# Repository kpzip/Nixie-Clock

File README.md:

# Nixie-Clock
Clock using IN-16 Nixie Tubes

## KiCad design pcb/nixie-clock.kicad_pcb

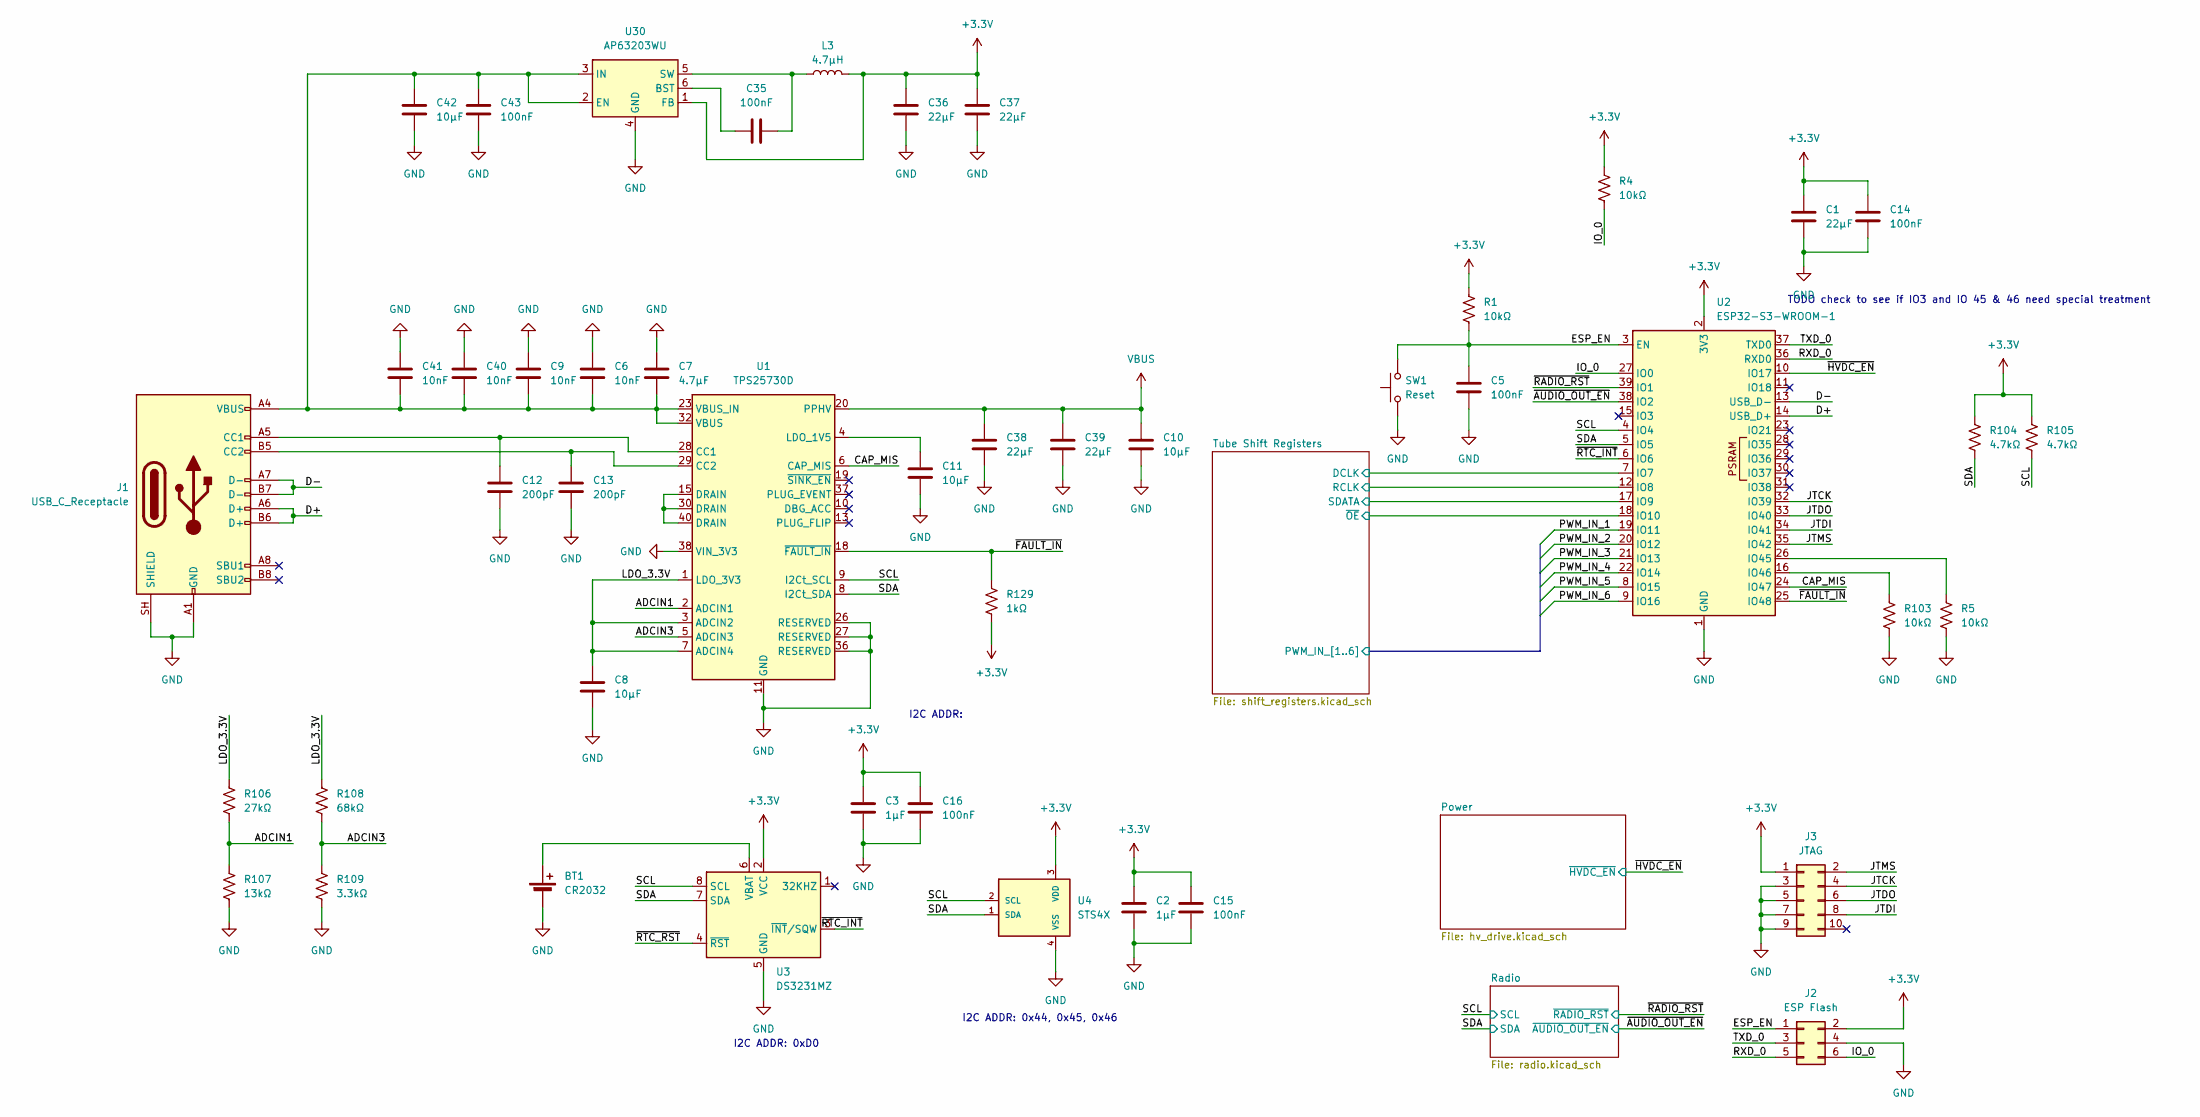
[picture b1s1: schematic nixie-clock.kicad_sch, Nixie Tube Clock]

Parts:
BT1: CR2032; BatteryHolder_MPD_BC2003_1x2032
C1, C36, C37, C38, C39: 22μF; C_0805_2012Metric
C2, C3: 1μF; C_0603_1608Metric
C5, C14, C15, C16, C35, C43: 100nF; C_0603_1608Metric
C6, C9, C40, C41: 10nF; C_0603_1608Metric
C7: 4.7μF; C_0805_2012Metric
C8, C10, C11, C42: 10μF; C_0805_2012Metric
C12, C13: 200pF; C_0603_1608Metric
J1: USB_C_Receptacle; USB_C_Receptacle_GCT_USB4105-xx-A_16P_TopMnt_Horizontal; Manufacturer Part Number USB4105-GF-A
J2: ESP Flash; IDC-Header_2x03_P2.54mm_Vertical
J3: JTAG; IDC-Header_2x05_P2.54mm_Vertical
L3: 4.7μH; L_0603_1608Metric_Pad1.05x0.95mm_HandSolder; Manufacturer Part Number LQM18PN4R7MFRL
R1, R4, R5, R103: 10kΩ; R_0603_1608Metric
R104, R105: 4.7kΩ; R_0603_1608Metric
R106: 27kΩ; R_0603_1608Metric
R107: 13kΩ; R_0603_1608Metric
R108: 68kΩ; R_0603_1608Metric
R109: 3.3kΩ; R_0603_1608Metric
R129: 1kΩ; R_0603_1608Metric
SW1: Reset; SW_PUSH_6mm; Manufacturer Part Number PTS645SL43-2 LFS
U1: TPS25730D; Texas_REF0038A_WQFN-38-2EP_6x4mm_P0.4
U2: ESP32-S3-WROOM-1; Manufacturer Part Number ESP32-S3-WROOM-1-N8R8
U3: DS3231MZ; SOIC-8_3.9x4.9mm_P1.27mm
U4: STS4X
U30: AP63203WU; TSOT-23-6

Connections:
+3.3V: C1.1, C2.1, C3.1, C14.1, C15.1, C16.1, C36.2, C37.2, J2.2, J3.1, L3.2, R1.1, R4.1, R104.1, R105.1, R129.2, U2.2 (3V3), U3.2 (VCC), U4.3 (VDD), U30.1 (FB); also elsewhere on the board
/ADCIN1: R106.2, R107.1, U1.2 (ADCIN1)
/ADCIN3: R108.2, R109.1, U1.5 (ADCIN3)
/CAP_MIS: U1.6 (CAP_MIS), U2.24 (IO47)
/D+: J1.A6 (D+), J1.B6 (D+), U2.14 (USB_D+)
/D-: J1.A7 (D-), J1.B7 (D-), U2.13 (USB_D-)
/ESP_EN: C5.1, J2.1, R1.2, SW1.2, U2.3 (EN)
/IO_0: J2.6, R4.2, U2.27 (IO0)
/JTCK: J3.4, U2.32 (IO39)
/JTDI: J3.8, U2.34 (IO41)
/JTDO: J3.6, U2.33 (IO40)
/JTMS: J3.2, U2.35 (IO42)
/LDO_3.3V: C8.2, R106.1, R108.1, U1.1 (LDO_3V3), U1.3 (ADCIN2), U1.7 (ADCIN4)
/RXD_0: J2.5, U2.36 (RXD0)
/SCL: R105.2, U1.9 (I2Ct_SCL), U2.4 (IO4), U3.8 (SCL), U4.2 (SCL); also elsewhere on the board
/SDA: R104.2, U1.8 (I2Ct_SDA), U2.5 (IO5), U3.7 (SDA), U4.1 (SDA); also elsewhere on the board
/TXD_0: J2.3, U2.37 (TXD0)
/Tube Shift Registers/DCLK: U2.7 (IO7); also elsewhere on the board
/Tube Shift Registers/PWM_IN_1: U2.19 (IO11); also elsewhere on the board
/Tube Shift Registers/PWM_IN_2: U2.20 (IO12); also elsewhere on the board
/Tube Shift Registers/PWM_IN_3: U2.21 (IO13); also elsewhere on the board
/Tube Shift Registers/PWM_IN_4: U2.22 (IO14); also elsewhere on the board
/Tube Shift Registers/PWM_IN_5: U2.8 (IO15); also elsewhere on the board
/Tube Shift Registers/PWM_IN_6: U2.9 (IO16); also elsewhere on the board
/Tube Shift Registers/RCLK: U2.12 (IO8); also elsewhere on the board
/Tube Shift Registers/SDATA: U2.17 (IO9); also elsewhere on the board
/Tube Shift Registers/~OE: U2.18 (IO10); also elsewhere on the board
/~AUDIO_OUT_EN: U2.38 (IO2); also elsewhere on the board
/~FAULT_IN: R129.1, U1.18 (~FAULT_IN), U2.25 (IO48)
/~HVDC_EN: U2.10 (IO17); also elsewhere on the board
/~RADIO_RST: U2.39 (IO1); also elsewhere on the board
/~RTC_INT: U2.6 (IO6), U3.3 (~INT/SQW)
/~RTC_RST: U3.4 (~RST)
unnamed: BT1.1 (+), U3.6 (VBAT)
unnamed: C12.2, J1.A5 (CC1), U1.28 (CC1)
unnamed: C13.2, J1.B5 (CC2), U1.29 (CC2)
unnamed: U1.15 (DRAIN), U1.30 (DRAIN), U1.40 (DRAIN)
unnamed: C11.1, U1.4 (LDO_1V5)
unnamed: C6.2, C7.2, C9.2, C40.2, C41.2, C42.1, C43.1, J1.A4 (VBUS), J1.A9 (VBUS), J1.B4 (VBUS), J1.B9 (VBUS), U1.23 (VBUS_IN), U1.32 (VBUS), U30.2 (EN), U30.3 (IN)
unnamed: R5.1, U2.26 (IO45)
unnamed: R103.1, U2.16 (IO46)
unnamed: C35.1, U30.6 (BST)
unnamed: C35.2, L3.1, U30.5 (SW)
VBUS: C10.1, C38.2, C39.2, U1.20 (PPHV); also elsewhere on the board

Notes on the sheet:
I2C ADDR: 0x44, 0x45, 0x46
TODO check to see if IO3 and IO 45 & 46 need special treatment
I2C ADDR: 0xD0
I2C ADDR:

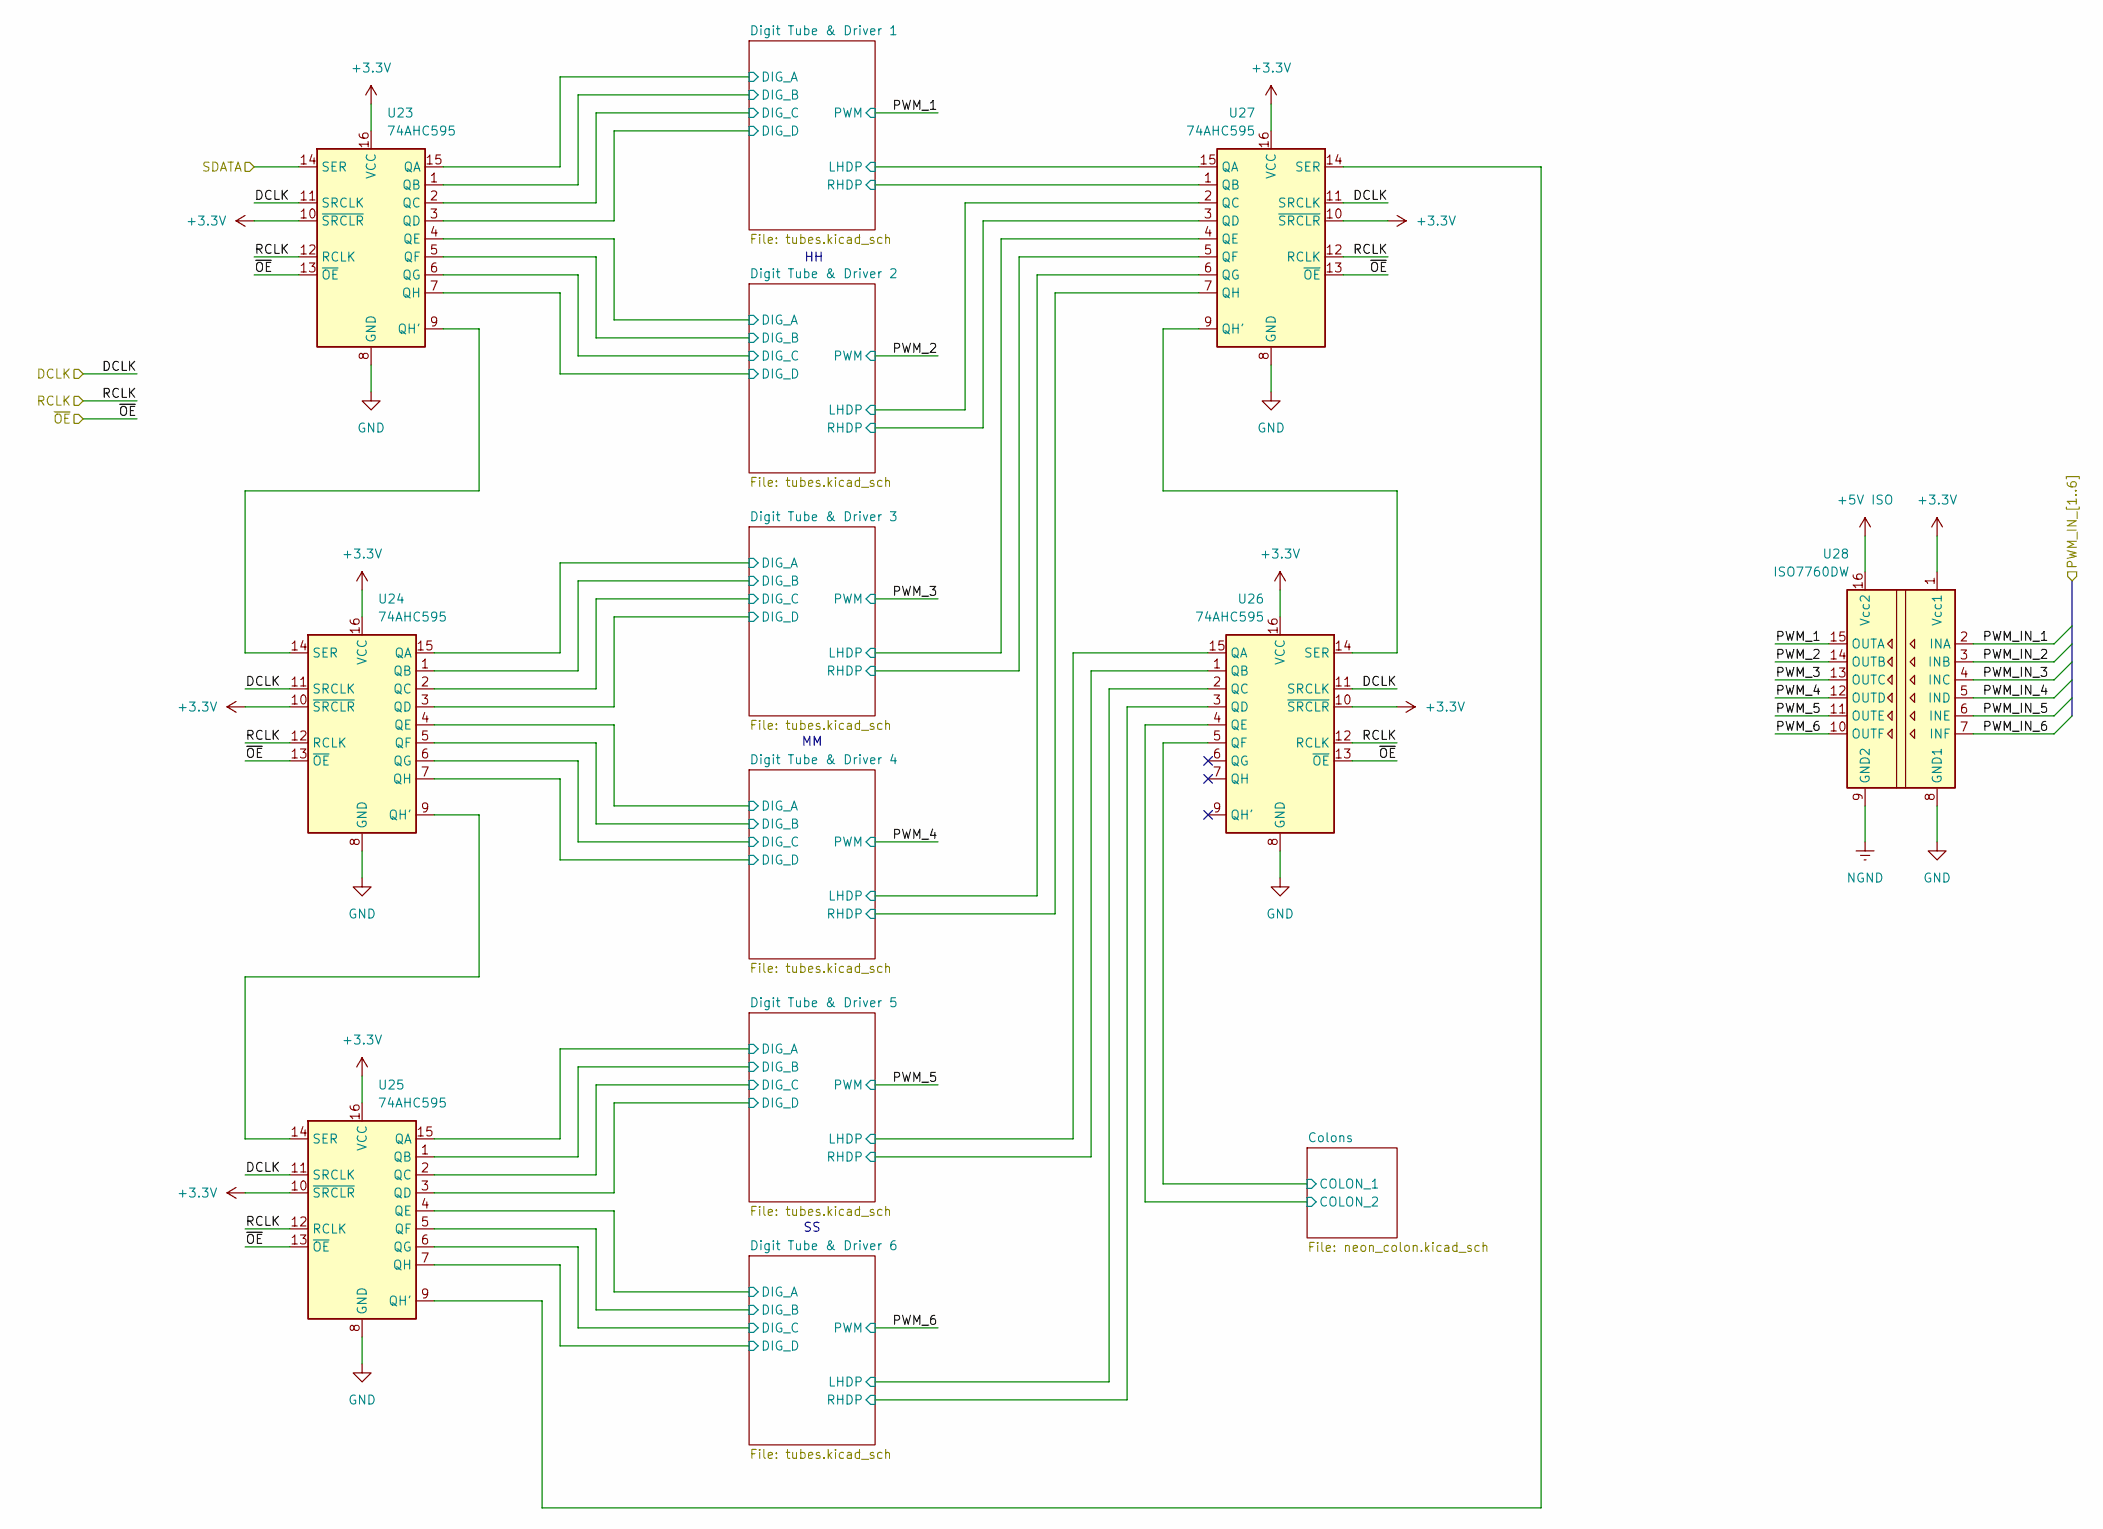
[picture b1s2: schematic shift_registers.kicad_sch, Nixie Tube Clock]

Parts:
U23, U24, U25, U26, U27: 74AHC595; SOIC-16_3.9x9.9mm_P1.27mm
U28: ISO7760DW; SOIC-16W_7.5x10.3mm_P1.27mm

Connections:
+3.3V: U23.10 (~SRCLR), U23.16 (VCC), U24.10 (~SRCLR), U24.16 (VCC), U25.10 (~SRCLR), U25.16 (VCC), U26.10 (~SRCLR), U26.16 (VCC), U27.10 (~SRCLR), U27.16 (VCC), U28.1 (Vcc1); also elsewhere on the board
+5V ISO: U28.16 (Vcc2); also elsewhere on the board
/Tube Shift Registers/Colons/COLON_1: U26.5 (QF); also elsewhere on the board
/Tube Shift Registers/Colons/COLON_2: U26.4 (QE); also elsewhere on the board
/Tube Shift Registers/DCLK: U23.11 (SRCLK), U24.11 (SRCLK), U25.11 (SRCLK), U26.11 (SRCLK), U27.11 (SRCLK); also elsewhere on the board
/Tube Shift Registers/Digit Tube & Driver 1/DIG_A: U23.15 (QA); also elsewhere on the board
/Tube Shift Registers/Digit Tube & Driver 1/DIG_B: U23.1 (QB); also elsewhere on the board
/Tube Shift Registers/Digit Tube & Driver 1/DIG_C: U23.2 (QC); also elsewhere on the board
/Tube Shift Registers/Digit Tube & Driver 1/DIG_D: U23.3 (QD); also elsewhere on the board
/Tube Shift Registers/Digit Tube & Driver 1/LHDP: U27.15 (QA); also elsewhere on the board
/Tube Shift Registers/Digit Tube & Driver 1/RHDP: U27.1 (QB); also elsewhere on the board
/Tube Shift Registers/Digit Tube & Driver 2/DIG_A: U23.4 (QE); also elsewhere on the board
/Tube Shift Registers/Digit Tube & Driver 2/DIG_B: U23.5 (QF); also elsewhere on the board
/Tube Shift Registers/Digit Tube & Driver 2/DIG_C: U23.6 (QG); also elsewhere on the board
/Tube Shift Registers/Digit Tube & Driver 2/DIG_D: U23.7 (QH); also elsewhere on the board
/Tube Shift Registers/Digit Tube & Driver 2/LHDP: U27.2 (QC); also elsewhere on the board
/Tube Shift Registers/Digit Tube & Driver 2/RHDP: U27.3 (QD); also elsewhere on the board
/Tube Shift Registers/Digit Tube & Driver 3/DIG_A: U24.15 (QA); also elsewhere on the board
/Tube Shift Registers/Digit Tube & Driver 3/DIG_B: U24.1 (QB); also elsewhere on the board
/Tube Shift Registers/Digit Tube & Driver 3/DIG_C: U24.2 (QC); also elsewhere on the board
/Tube Shift Registers/Digit Tube & Driver 3/DIG_D: U24.3 (QD); also elsewhere on the board
/Tube Shift Registers/Digit Tube & Driver 3/LHDP: U27.4 (QE); also elsewhere on the board
/Tube Shift Registers/Digit Tube & Driver 3/RHDP: U27.5 (QF); also elsewhere on the board
/Tube Shift Registers/Digit Tube & Driver 4/DIG_A: U24.4 (QE); also elsewhere on the board
/Tube Shift Registers/Digit Tube & Driver 4/DIG_B: U24.5 (QF); also elsewhere on the board
/Tube Shift Registers/Digit Tube & Driver 4/DIG_C: U24.6 (QG); also elsewhere on the board
/Tube Shift Registers/Digit Tube & Driver 4/DIG_D: U24.7 (QH); also elsewhere on the board
/Tube Shift Registers/Digit Tube & Driver 4/LHDP: U27.6 (QG); also elsewhere on the board
/Tube Shift Registers/Digit Tube & Driver 4/RHDP: U27.7 (QH); also elsewhere on the board
/Tube Shift Registers/Digit Tube & Driver 5/DIG_A: U25.15 (QA); also elsewhere on the board
/Tube Shift Registers/Digit Tube & Driver 5/DIG_B: U25.1 (QB); also elsewhere on the board
/Tube Shift Registers/Digit Tube & Driver 5/DIG_C: U25.2 (QC); also elsewhere on the board
/Tube Shift Registers/Digit Tube & Driver 5/DIG_D: U25.3 (QD); also elsewhere on the board
/Tube Shift Registers/Digit Tube & Driver 5/LHDP: U26.15 (QA); also elsewhere on the board
/Tube Shift Registers/Digit Tube & Driver 5/RHDP: U26.1 (QB); also elsewhere on the board
/Tube Shift Registers/Digit Tube & Driver 6/DIG_A: U25.4 (QE); also elsewhere on the board
/Tube Shift Registers/Digit Tube & Driver 6/DIG_B: U25.5 (QF); also elsewhere on the board
/Tube Shift Registers/Digit Tube & Driver 6/DIG_C: U25.6 (QG); also elsewhere on the board
/Tube Shift Registers/Digit Tube & Driver 6/DIG_D: U25.7 (QH); also elsewhere on the board
/Tube Shift Registers/Digit Tube & Driver 6/LHDP: U26.2 (QC); also elsewhere on the board
/Tube Shift Registers/Digit Tube & Driver 6/RHDP: U26.3 (QD); also elsewhere on the board
/Tube Shift Registers/PWM_1: U28.15 (OUTA); also elsewhere on the board
/Tube Shift Registers/PWM_2: U28.14 (OUTB); also elsewhere on the board
/Tube Shift Registers/PWM_3: U28.13 (OUTC); also elsewhere on the board
/Tube Shift Registers/PWM_4: U28.12 (OUTD); also elsewhere on the board
/Tube Shift Registers/PWM_5: U28.11 (OUTE); also elsewhere on the board
/Tube Shift Registers/PWM_6: U28.10 (OUTF); also elsewhere on the board
/Tube Shift Registers/PWM_IN_1: U28.2 (INA); also elsewhere on the board
/Tube Shift Registers/PWM_IN_2: U28.3 (INB); also elsewhere on the board
/Tube Shift Registers/PWM_IN_3: U28.4 (INC); also elsewhere on the board
/Tube Shift Registers/PWM_IN_4: U28.5 (IND); also elsewhere on the board
/Tube Shift Registers/PWM_IN_5: U28.6 (INE); also elsewhere on the board
/Tube Shift Registers/PWM_IN_6: U28.7 (INF); also elsewhere on the board
/Tube Shift Registers/RCLK: U23.12 (RCLK), U24.12 (RCLK), U25.12 (RCLK), U26.12 (RCLK), U27.12 (RCLK); also elsewhere on the board
/Tube Shift Registers/SDATA: U23.14 (SER); also elsewhere on the board
/Tube Shift Registers/~OE: U23.13 (~OE), U24.13 (~OE), U25.13 (~OE), U26.13 (~OE), U27.13 (~OE); also elsewhere on the board
unnamed: U23.9 (QH'), U24.14 (SER)
unnamed: U24.9 (QH'), U25.14 (SER)
unnamed: U25.9 (QH'), U27.14 (SER)
unnamed: U26.14 (SER), U27.9 (QH')

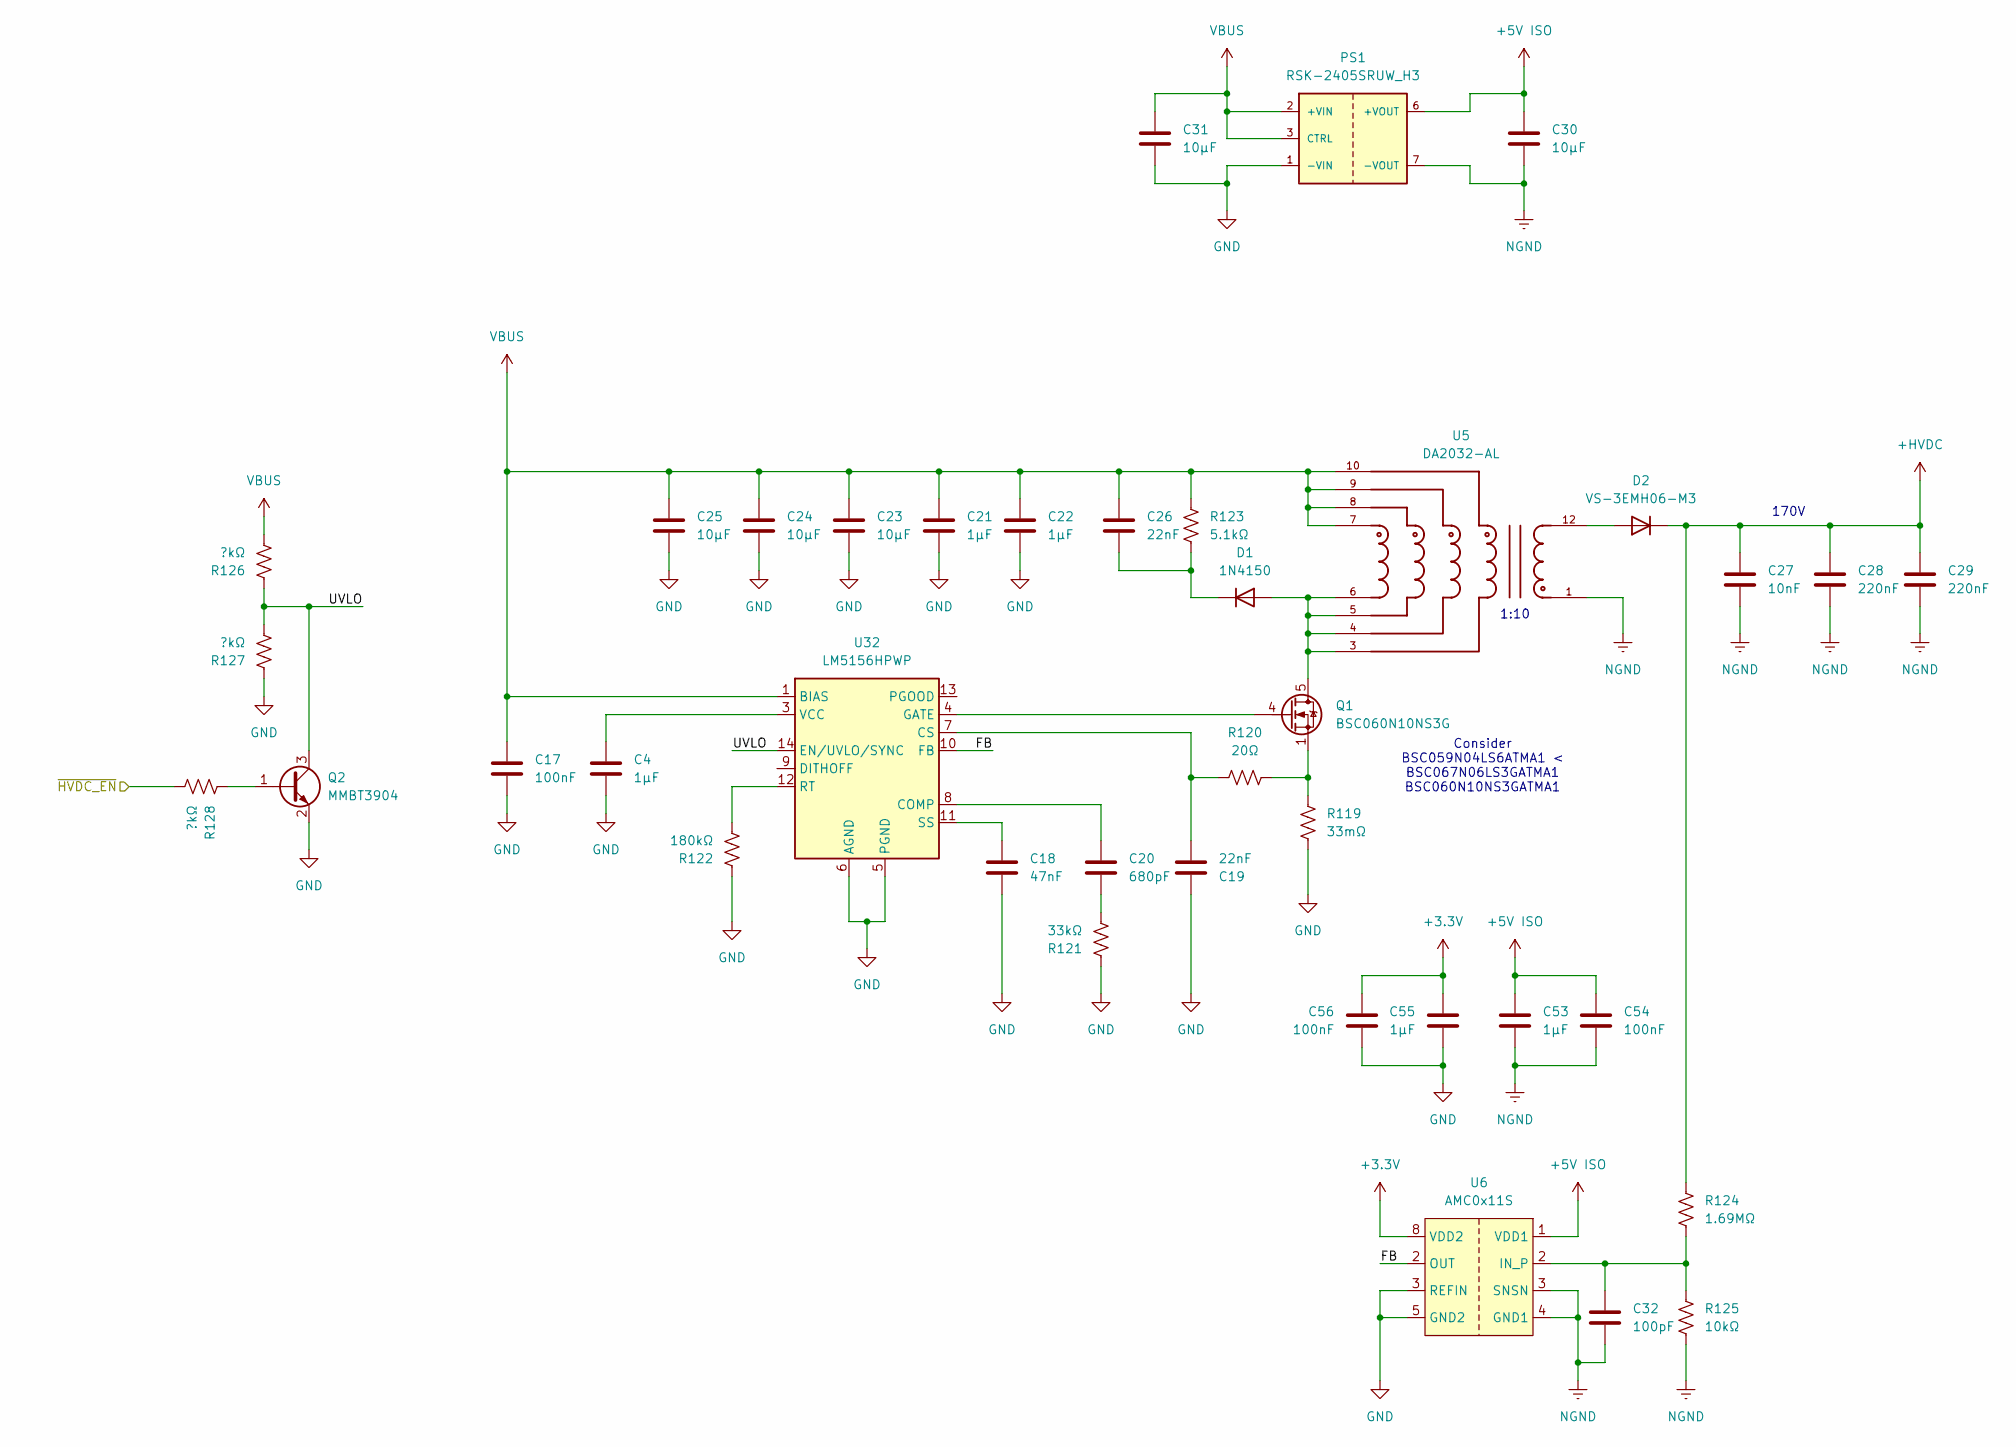
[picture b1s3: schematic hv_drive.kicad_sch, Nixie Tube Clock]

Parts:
C4, C21, C22, C53, C55: 1μF; C_0603_1608Metric
C17, C54, C56: 100nF; C_0603_1608Metric
C18: 47nF; C_0603_1608Metric
C19, C26: 22nF; C_0603_1608Metric
C20: 680pF; C_0603_1608Metric
C23, C24, C25, C30, C31: 10μF; C_0805_2012Metric
C27: 10nF; C_0603_1608Metric
C28, C29: 220nF; C_0603_1608Metric
C32: 100pF; C_0603_1608Metric
D1: 1N4150; Nexperia_CFP3_SOD-123W; Manufacturer Part Number 1N4150W-E3-08
D2: VS-3EMH06-M3; D_SMA_Handsoldering; Manufacturer Part Number VS-3EMH06-M3/5AT
PS1: RSK-2405SRUW_H3; CONV_RSK-2405SRUW_H3; PARTREV 0/2023
Q1: BSC060N10NS3G; TDSON-8-1; Manufacturer Part Number BSC060N10NS3GATMA1
Q2: MMBT3904; SOT-23
R119: 33mΩ; R_0603_1608Metric
R120: 20Ω; R_0603_1608Metric
R121: 33kΩ; R_0603_1608Metric
R122: 180kΩ; R_0603_1608Metric
R123: 5.1kΩ; R_0603_1608Metric
R124: 1.69MΩ; R_0603_1608Metric
R125: 10kΩ; R_0603_1608Metric
R126, R127, R128: ?kΩ; R_0603_1608Metric
U5: DA2032-AL
U6: AMC0x11S; SOIC-8_3.9x4.9mm_P1.27mm; Manufacturer Part Number AMC0311S
U32: LM5156HPWP; Texas_HTSSOP-14-1EP_4.4x5mm_P0.65mm_EP3.4x5mm_Mask3.155x3.2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

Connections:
+3.3V: C55.1, C56.1, U6.8 (VDD2); also elsewhere on the board
+5V ISO: C30.1, C53.1, C54.1, PS1.6 (+VOUT), U6.1 (VDD1); also elsewhere on the board
+HVDC: C27.1, C28.1, C29.1, D2.1 (K), R124.2; also elsewhere on the board
/Power/UVLO: Q2.3 (C), R126.1, R127.2, U32.14 (EN/UVLO/SYNC)
/~HVDC_EN: R128.2; also elsewhere on the board
unnamed: C20.2, R121.2
unnamed: D1.2 (A), Q1.5 (D), U5.3, U5.4, U5.5, U5.6
unnamed: C26.2, D1.1 (K), R123.2
unnamed: D2.2 (A), U5.12
unnamed: PS1.5 (NC), PS1.8 (NC)
unnamed: Q1.4 (G), U32.4 (GATE)
unnamed: Q1.1 (S), Q1.2 (S), Q1.3 (S), R119.1, R120.2
unnamed: Q2.1 (B), R128.1
unnamed: C20.1, U32.8 (COMP)
unnamed: C19.2, R120.1, U32.7 (CS)
unnamed: R122.2, U32.12 (RT)
unnamed: C18.1, U32.11 (SS)
unnamed: C4.1, U32.3 (VCC)
VBUS: C17.1, C21.1, C22.1, C23.1, C24.1, C25.1, C26.1, C31.1, PS1.2 (+VIN), PS1.3 (CTRL), R123.1, R126.2, U5.7, U5.8, U5.9, U5.10, U32.1 (BIAS); also elsewhere on the board

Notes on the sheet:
1:10
170V
Consider BSC059N04LS6ATMA1 < BSC067N06LS3GATMA1 BSC060N10NS3GATMA1

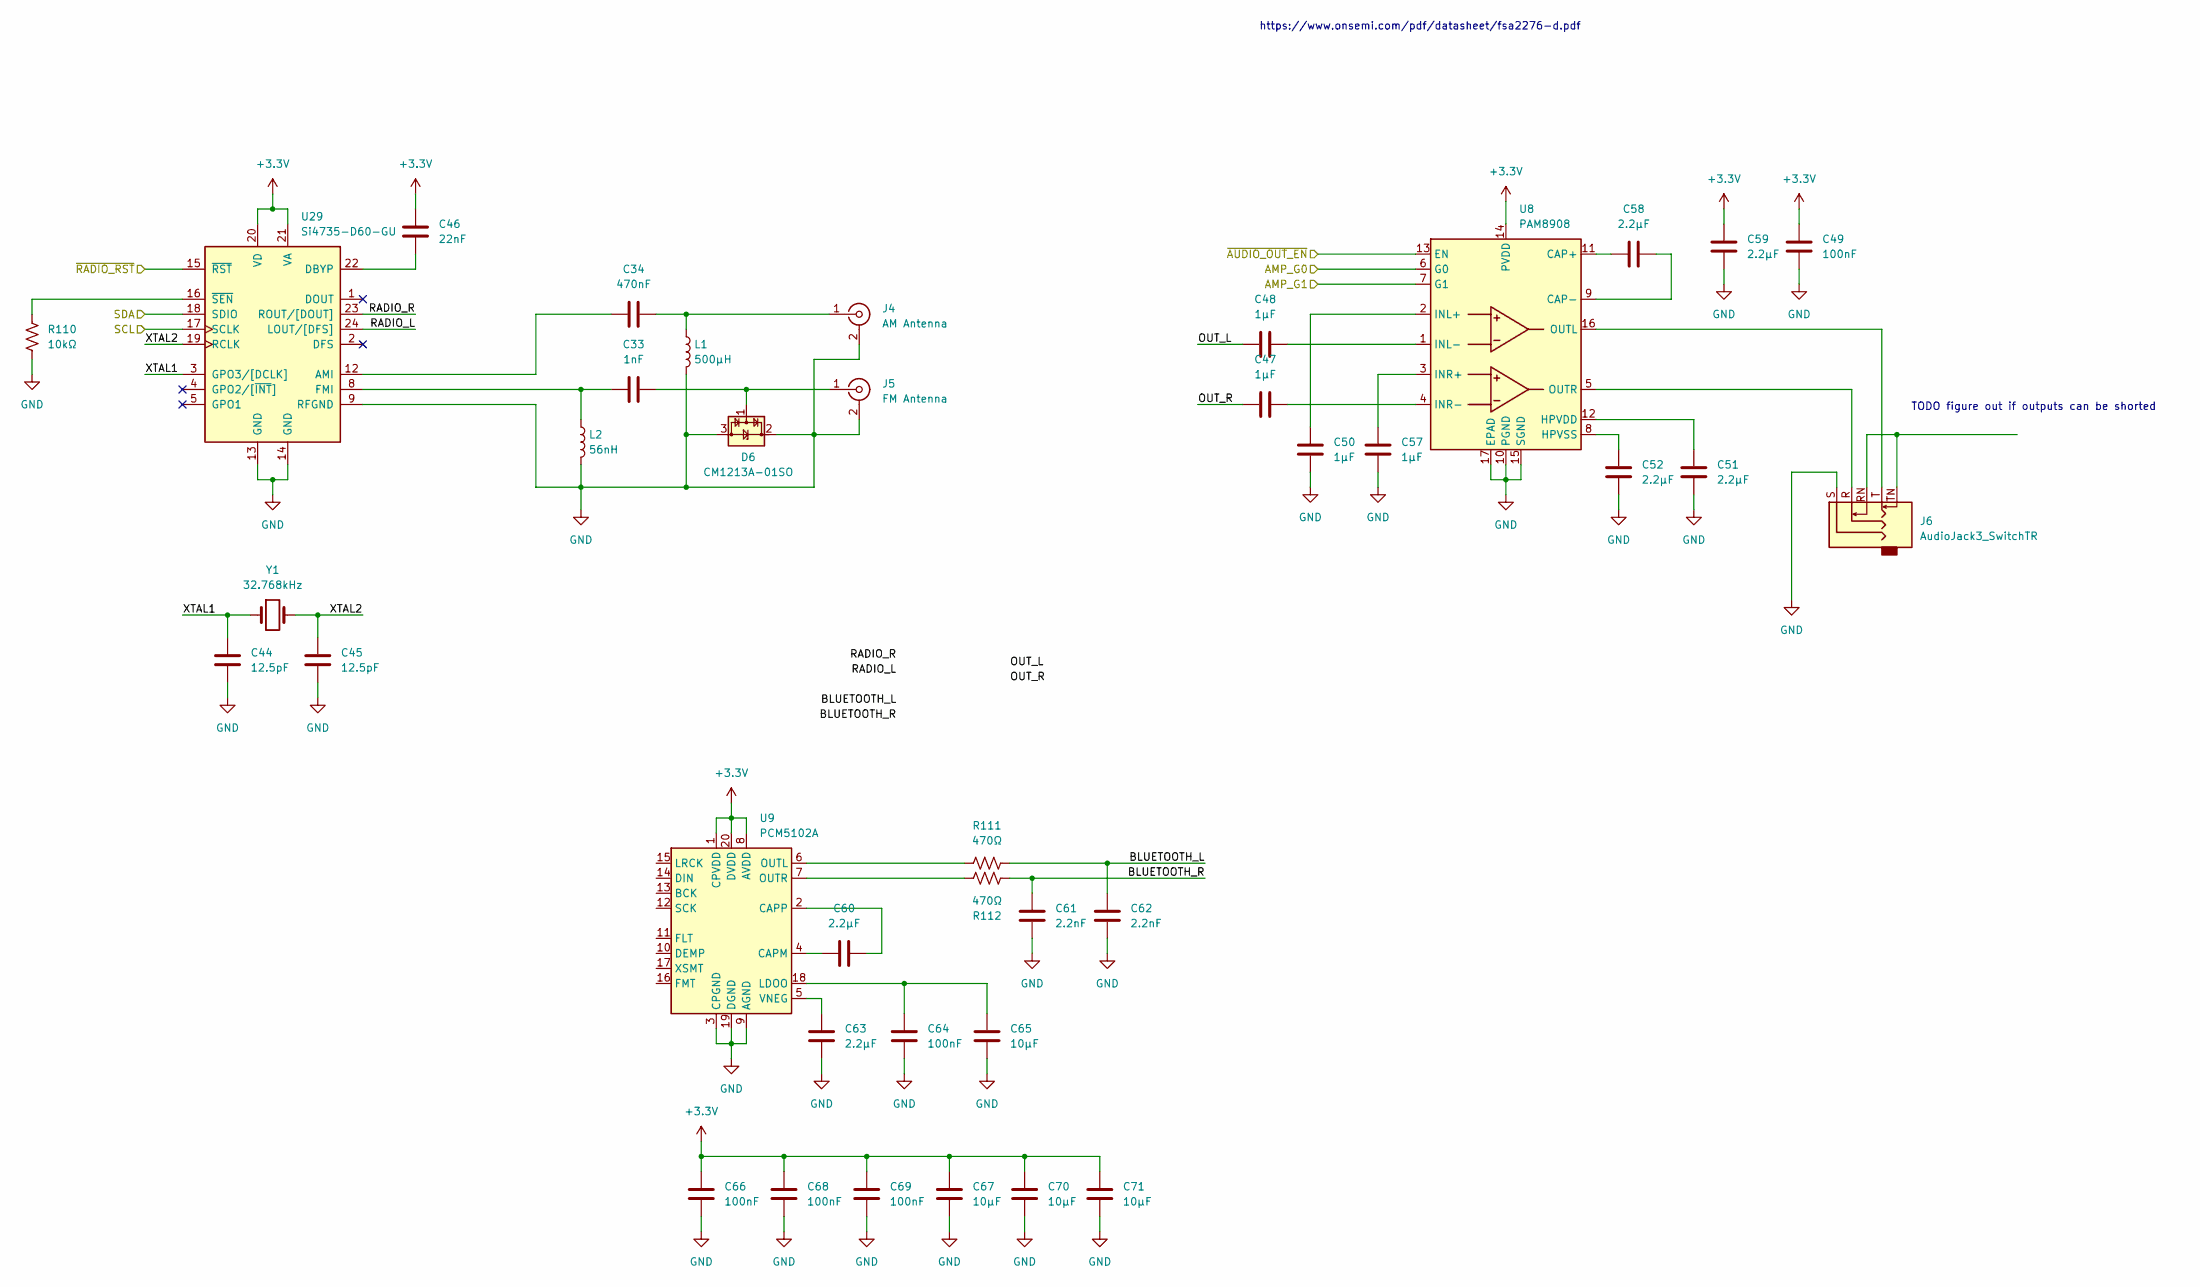
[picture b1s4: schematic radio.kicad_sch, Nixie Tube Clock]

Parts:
C33: 1nF; C_0603_1608Metric
C34: 470nF; C_0603_1608Metric
C44, C45: 12.5pF; C_0603_1608Metric
C46: 22nF; C_0603_1608Metric
C47, C48, C50, C57: 1μF; C_0603_1608Metric
C49, C64, C66, C68, C69: 100nF; C_0603_1608Metric
C51, C52, C58, C59, C60, C63: 2.2μF; C_0603_1608Metric
C61, C62: 2.2nF; C_0603_1608Metric
C65, C67, C70, C71: 10μF; C_0805_2012Metric
D6: CM1213A-01SO; SOT-23
J4: AM Antenna; BNC_TEConnectivity_1478204_Vertical
J5: FM Antenna; BNC_TEConnectivity_1478204_Vertical
J6: AudioJack3_SwitchTR; Jack_3.5mm_CUI_SJ1-3535NG_Horizontal
L1: 500μH
L2: 56nH
R110: 10kΩ; R_0603_1608Metric
R111, R112: 470Ω; R_0603_1608Metric
U8: PAM8908; QFN-16-1EP_3x3mm_P0.5mm_EP1.7x1.7mm
U9: PCM5102A; TSSOP-20_4.4x6.5mm_P0.65mm
U29: Si4735-D60-GU; SSOP-24_3.9x8.7mm_P0.635mm
Y1: 32.768kHz; Crystal_SMD_3215-2Pin_3.2x1.5mm; Manufacturer Part Number ECS-.327-12.5-34B-TR

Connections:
+3.3V: C46.2, C49.2, C59.1, C66.1, C67.1, C68.1, C69.1, C70.1, C71.1, U8.14 (PVDD), U9.1 (CPVDD), U9.8 (AVDD), U9.20 (DVDD), U29.20 (VD), U29.21 (VA); also elsewhere on the board
/Radio/AMP_G0: U8.6 (G0)
/Radio/AMP_G1: U8.7 (G1)
/Radio/BLUETOOTH_L: C62.1, R111.1
/Radio/BLUETOOTH_R: C61.1, R112.1
/Radio/OUT_L: C48.2
/Radio/OUT_R: C47.2
/Radio/RADIO_L: U29.24 (LOUT/[DFS])
/Radio/RADIO_R: U29.23 (ROUT/[DOUT])
/Radio/XTAL1: C44.2, U29.3 (GPO3/[DCLK]), Y1.1
/Radio/XTAL2: C45.2, U29.19 (RCLK), Y1.2
/SCL: U29.17 (SCLK); also elsewhere on the board
/SDA: U29.18 (SDIO); also elsewhere on the board
/~AUDIO_OUT_EN: U8.13 (EN); also elsewhere on the board
/~RADIO_RST: U29.15 (~RST); also elsewhere on the board
unnamed: C33.2, D6.1 (CH1), J5.1 (In)
unnamed: C34.2, J4.1 (In), L1.1
unnamed: J6.RN, J6.TN
unnamed: C58.2, U8.11 (CAP+)
unnamed: C58.1, U8.9 (CAP-)
unnamed: C51.2, U8.12 (HPVDD)
unnamed: C52.2, U8.8 (HPVSS)
unnamed: C50.1, U8.2 (INL+)
unnamed: C48.1, U8.1 (INL-)
unnamed: C57.1, U8.3 (INR+)
unnamed: C47.1, U8.4 (INR-)
unnamed: J6.T, U8.16 (OUTL)
unnamed: J6.R, U8.5 (OUTR)
unnamed: C60.2, U9.4 (CAPM)
unnamed: C60.1, U9.2 (CAPP)
unnamed: C64.1, C65.1, U9.18 (LDOO)
unnamed: R111.2, U9.6 (OUTL)
unnamed: R112.2, U9.7 (OUTR)
unnamed: C63.1, U9.5 (VNEG)
unnamed: C34.1, U29.12 (AMI)
unnamed: C46.1, U29.22 (DBYP)
unnamed: C33.1, L2.1, U29.8 (FMI)
unnamed: R110.1, U29.16 (~SEN)

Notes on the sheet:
https://www.onsemi.com/pdf/datasheet/fsa2276-d.pdf
TODO figure out if outputs can be shorted
